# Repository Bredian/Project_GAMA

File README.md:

# Project_GAMA

We are making 8-bit game system on AVR.

Roles on this project as follows:

Gruzdev Fedor - SID chip programming (asm) and general hardware design - Attiny45

Krylov Alexander - Main Processing Unit programming (C lang (+asm maybe)) - Atmega (model unknown for now)

Savostenok Zlata - Controller interface programming (C lang) - Attiny45 + 7400 series logic

Buchnev Arseniy - Hardware maintenance and soldering

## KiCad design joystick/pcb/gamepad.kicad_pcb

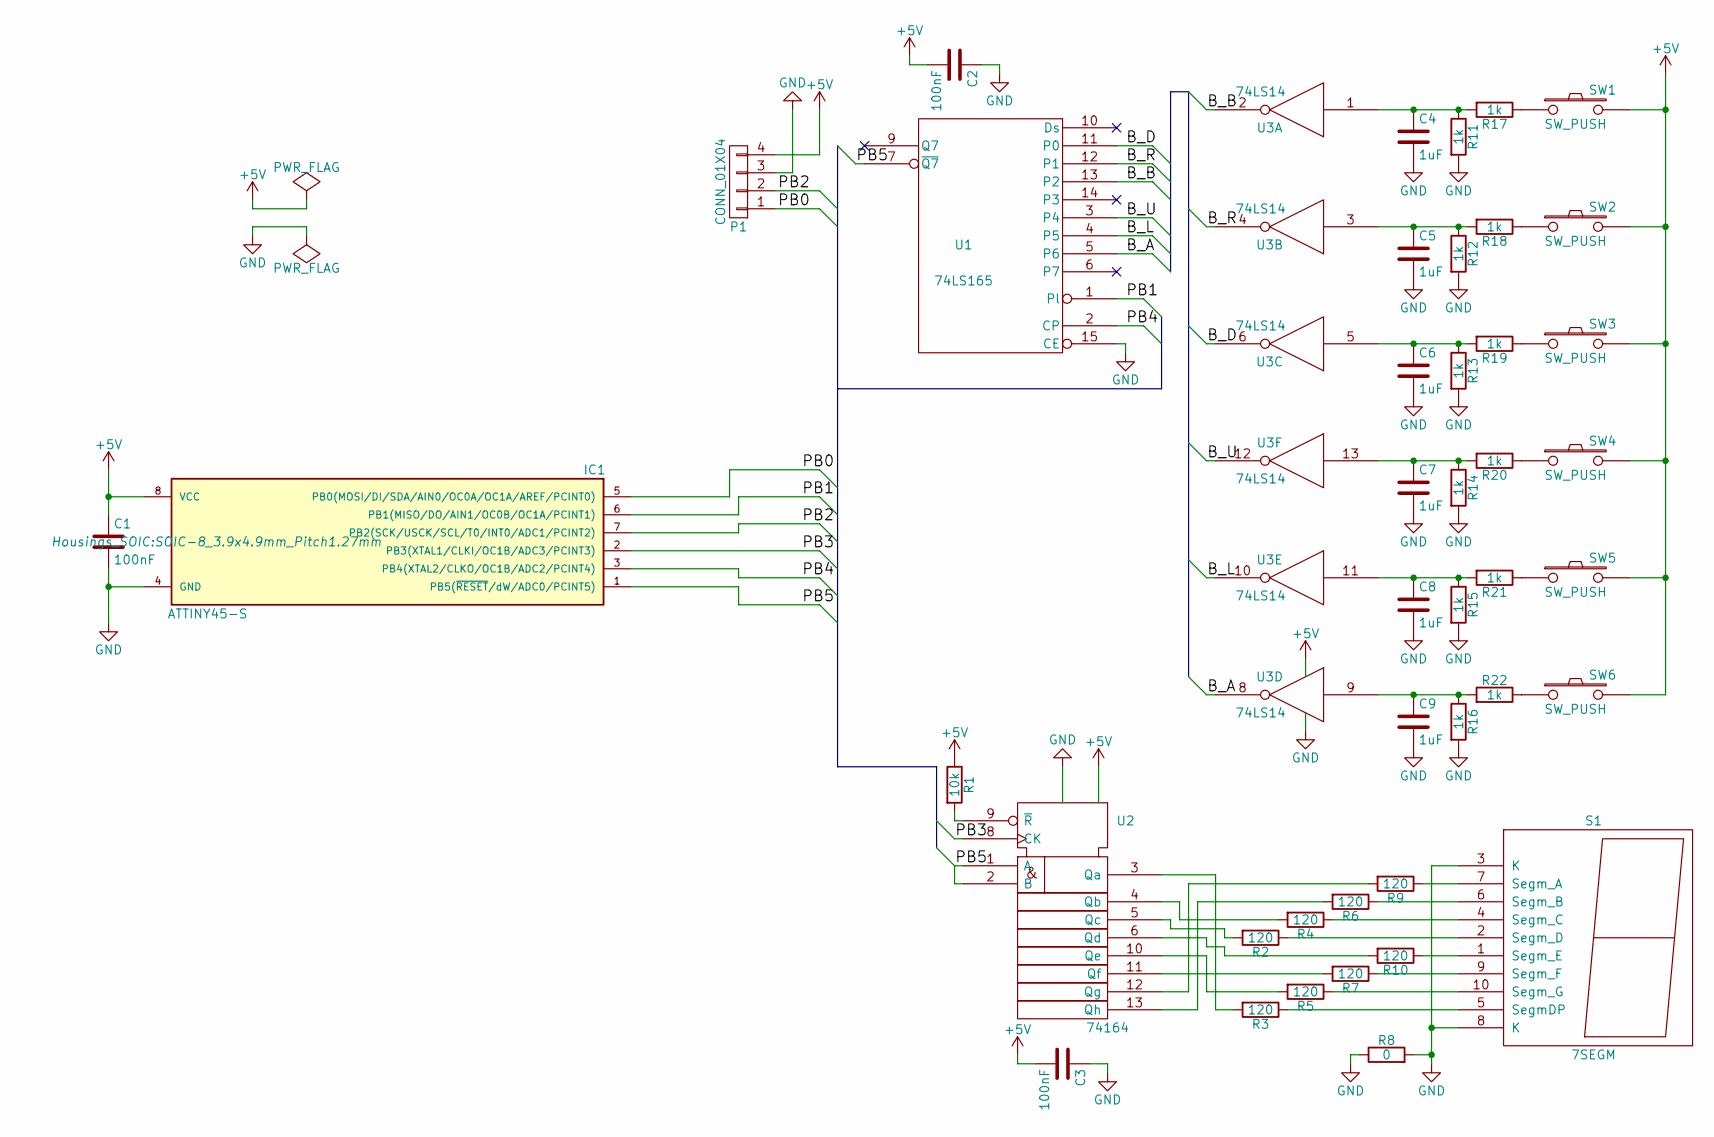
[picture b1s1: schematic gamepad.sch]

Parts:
C1, C2, C3: 100nF; C_0805_HandSoldering
C4, C5, C6, C7, C8, C9: 1uF; C_0805_HandSoldering
IC1: ATTINY45-S; SOIC-8_3.9x4.9mm_Pitch1.27mm
P1: CONN_01X04; Pin_Header_Angled_1x04
R1: 10k; R_0805_HandSoldering
R2, R3, R4, R5, R6, R7, R9, R10: 120; R_0805_HandSoldering
R8: 0; R_0805_HandSoldering
R11, R12, R13, R14, R15, R16, R17, R18, R19, R20, R21, R22: 1k; R_0805_HandSoldering
S1: 7SEGM; 7SegmentLED_LTS6760_LTS6780
SW1, SW2, SW3, SW4, SW5, SW6: SW_PUSH; SW_PUSH_SMALL
U1: 74LS165; SO-16-N
U2: 74164; SOIC-14_3.9x8.7mm_Pitch1.27mm
U3: 74LS14; SOIC-14_3.9x8.7mm_Pitch1.27mm

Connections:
+5V: C1.1, C2.2, C3.2, IC1.8 (VCC), P1.4, R1.1, SW1.2, SW2.2, SW3.2, SW4.2, SW5.2, SW6.2, U1.16 (VCC), U2.14 (Vdd), U3.14 (VCC)
/B_A: U1.5 (P6), U3.8
/B_B: U1.13 (P2), U3.2
/B_D: U1.11 (P0), U3.6
/B_L: U1.4 (P5), U3.10
/B_R: U1.12 (P1), U3.4
/B_U: U1.3 (P4), U3.12
/PB0: IC1.5 (PB0(MOSI/DI/SDA/AIN0/OC0A/OC1A/AREF/PCI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), P1.1
/PB1: IC1.6 (PB1(MISO/DO/AIN1/OC0B/OC1A/PCINT1)), U1.1 (Pl)
/PB2: IC1.7 (PB2(SCK/USCK/SCL/T0/INT0/ADC1/PCINT2)), P1.2
/PB3: IC1.2 (PB3(XTAL1/CLKI/OC1B/ADC3/PCINT3)), U2.8 (CK)
/PB4: IC1.3 (PB4(XTAL2/CLKO/OC1B/ADC2/PCINT4)), U1.2 (CP)
/PB5: IC1.1 (PB5(~RESET~/dW/ADC0/PCINT5)), U1.7 (~Q7), U2.1 (A), U2.2 (B)
GND: C1.2, C2.1, C3.1, C4.2, C5.2, C6.2, C7.2, C8.2, C9.2, IC1.4 (GND), P1.3, R8.1, R8.2, R11.2, R12.2, R13.2, R14.2, R15.2, R16.2, S1.3 (K), S1.8 (K), U1.8 (GND), U1.15 (CE), U2.7 (Vss), U3.7 (GND)
unnamed: C4.1, R11.1, R17.2, U3.1
unnamed: C5.1, R12.1, R18.2, U3.3
unnamed: C6.1, R13.1, R19.2, U3.5
unnamed: C7.1, R14.1, R20.2, U3.13
unnamed: C8.1, R15.1, R21.2, U3.11
unnamed: C9.1, R16.1, R22.2, U3.9
unnamed: R1.2, U2.9 (~R)
unnamed: R2.1, S1.2 (Segm_D)
unnamed: R2.2, U2.5 (Qc)
unnamed: R3.1, S1.5 (SegmDP)
unnamed: R3.2, U2.3 (Qa)
unnamed: R4.1, S1.4 (Segm_C)
unnamed: R4.2, U2.4 (Qb)
unnamed: R5.1, S1.10 (Segm_G)
unnamed: R5.2, U2.10 (Qe)
unnamed: R6.1, S1.6 (Segm_B)
unnamed: R6.2, U2.13 (Qh)
unnamed: R7.1, S1.9 (Segm_F)
unnamed: R7.2, U2.11 (Qf)
unnamed: R9.1, S1.7 (Segm_A)
unnamed: R9.2, U2.12 (Qg)
unnamed: R10.1, S1.1 (Segm_E)
unnamed: R10.2, U2.6 (Qd)
unnamed: R17.1, SW1.1
unnamed: R18.1, SW2.1
unnamed: R19.1, SW3.1
unnamed: R20.1, SW4.1
unnamed: R21.1, SW5.1
unnamed: R22.1, SW6.1

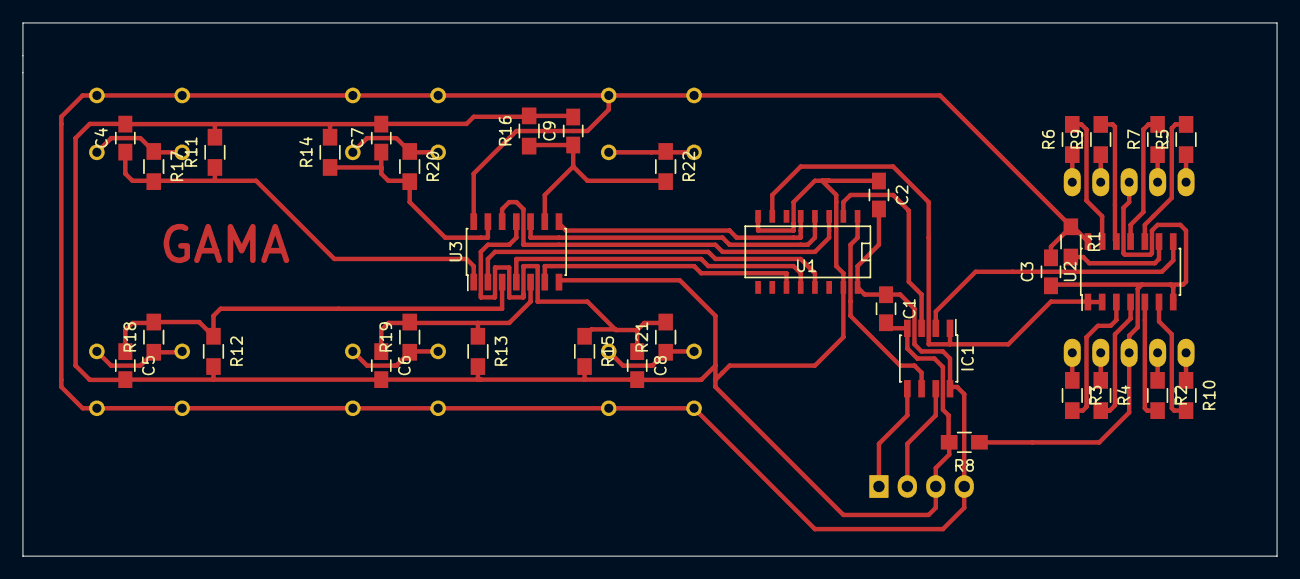
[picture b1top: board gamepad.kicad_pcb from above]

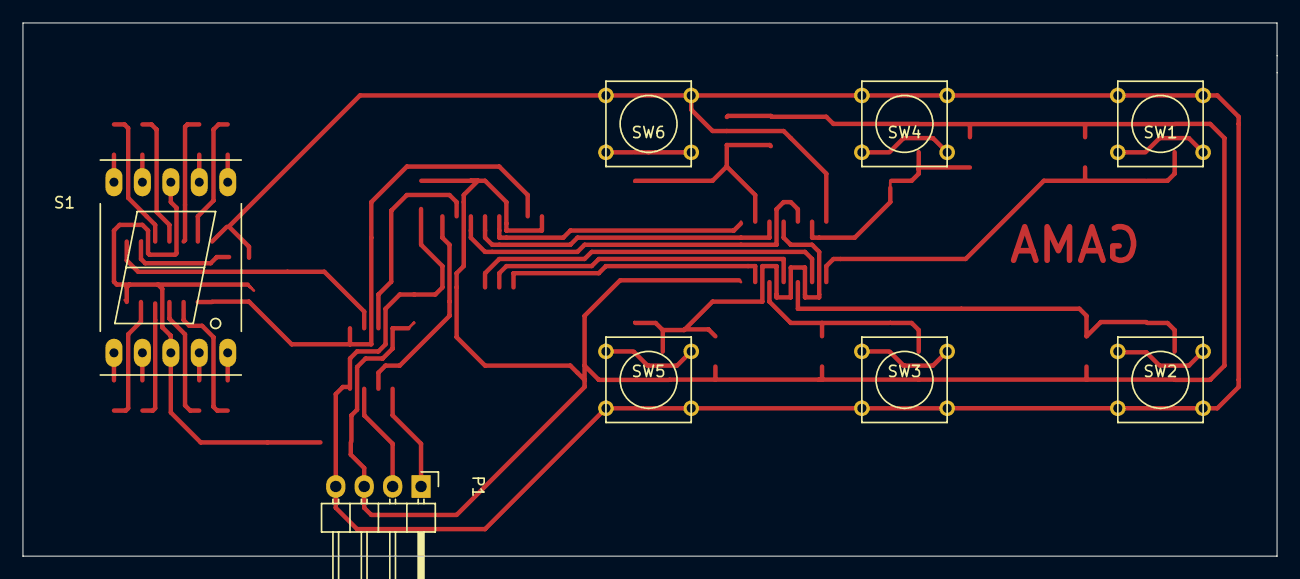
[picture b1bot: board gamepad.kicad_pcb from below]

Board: 2 copper layers, 112.0 x 47.6 mm, 43 parts (8 on the bottom side), 43 nets.

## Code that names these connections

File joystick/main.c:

#include <avr/io.h>
#include <avr/interrupt.h>
#include <avr/cpufunc.h>
#include "USI_TWI_Slave.h"

#define SLAVE_ADDR 0x02

#define SAMPLE PB1
#define CLK_7SEG PB3
#define CLK_BUT PB4
#define DATA PB5


void main(void) __attribute__((noreturn));
uint8_t read_buttons(void);
void set_7seg(uint8_t num);


void main(void) {
	
	uint8_t tmp;
	
	DDRB = (1 << SAMPLE)|(1 << CLK_7SEG)|(1 << CLK_BUT)|(0 << DATA);//port directions
	PORTB = (1 << SAMPLE)|(1 << CLK_7SEG)|(1 << CLK_BUT);			//initial port states
	
	USI_TWI_Slave_Initialise(SLAVE_ADDR);
	
	sei();
	
	while(1) {
		
		if(USI_TWI_Data_In_Receive_Buffer())
			{
				tmp = USI_TWI_Receive_Byte();
				set_7seg(tmp);
			}
		
		tmp = read_buttons();
		USI_TWI_Transmit_Byte(tmp);	//not actually transmit, but put in buffer in order to transmit
	}
	
}


uint8_t read_buttons(void) {
	uint8_t buttons = 0, tmp = 0, i;
	
	DDRB &= ~(1 << DATA);			//will receive data
	
	PORTB &= ~(1 << SAMPLE);		//sampling buttons
	_NOP();
	_NOP();
	PORTB |= (1 << SAMPLE);
	
	PORTB &= ~(1 << CLK_BUT);		//clock goes down
	
	i = 0;
	
	while(i < 8) {
		PORTB |= (1 << CLK_BUT);	//clock goes up, data are clocked out of SR
		_NOP();
		_NOP();
		PORTB &= ~(1 << CLK_BUT);	//clock goes down
		
		tmp >>= 1;
		
		if((PORTB & (1 << DATA)) == 1)//getting data
			tmp |= (1 << 7);
		else
			tmp &= ~(1 << 7);
		
		i++;
	}
									//now we have buttons' state in tmp, LSB is P7 of SR
	
										//magic numbers! actually, we shake bits to get them in right places
	buttons |= (tmp & (1 << 5)) << 5;	//up
	buttons |= (tmp & (1 << 7)) << 4;	//down
	buttons |= (tmp & (1 << 6)) << 3;	//left
	buttons |= (tmp & (1 << 3)) << 2;	//right
	buttons |= (tmp & (1 << 2)) << 1;	//A
	buttons |= (tmp & (1 << 1)) << 0;	//B
	
	return buttons; 
}


void set_7seg(uint8_t num) {
	uint8_t tmp = 0;
	uint8_t i;
	
	tmp = (num & (1 << 4)) << 3;		//magic begins; tmp's MSB is dot
										//the only thing left now is number to display
	switch(num & 0b00001111) {					//loads of magic numbers follow. don't worry, it's just numbers to display 
		case 0: tmp = tmp | 0b01110111;
			break;
		case 1: tmp = tmp | 0b01000001;
			break;
		case 2: tmp = tmp | 0b00111011;
			break;
		case 3: tmp = tmp | 0b01101011;
			break;
		case 4: tmp = tmp | 0b01001101;
			break;
		case 5: tmp = tmp | 0b01101110;
			break;
		case 6: tmp = tmp | 0b01111110;
			break;
		case 7: tmp = tmp | 0b01000011;
			break;
		case 8: tmp = tmp | 0b01111111;
			break;
		case 9: tmp = tmp | 0b01101111;
			break;
		case 0x0a: tmp = tmp | 0b01011111;
			break;
		case 0x0b: tmp = tmp | 0b01111100;
			break;
		case 0x0c: tmp = tmp | 0b00110110;
			break;
		case 0x0d: tmp = tmp | 0b01111001;
			break;
		case 0x0e: tmp = tmp | 0b00111110;
			break;
		case 0x0f: tmp = tmp | 0b00011110;
			break;
	}
	
	DDRB |= (1 << DATA);			//now we send data
	for(i = 0; i < 8; i++) {		//shifting data out. LSB goes first
		PORTB &= ~(1 << CLK_7SEG);	//clock goes down
		if ((tmp & 1) == 1) PORTB |= (1 << DATA);
			else PORTB &= ~(1 << DATA);	//putting data bit on DATA
		_NOP();
		_NOP();
		PORTB |= (1 << CLK_7SEG);	//clock goes up, shifting our data bit out
	}
	
	return;
}

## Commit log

2017-02-19 Create Prototype
2017-03-07 INIT
    Added dirs for every part and current results.
2017-03-07 Added specs for SID and joystick
2017-03-13 Updated joystick's circuit
2017-04-03 Fixed hardware bug (74LS14 inputs were left floating) Changed schematics accordingly
2017-04-10 wrote part of TWI logic buffer operations and main interrupt are left also decided on slave address (0x03)
2017-04-12 wrote all TWI (I2C) parts mapped memory
2017-04-17 little optimization for TWI as we only send 1 byte, receiving part can be shortened a bit
2017-04-21 Modified TWI handler Wrote main program sceleton
2017-05-03 Started writing firmware. TWI communication - done (code from Atmel AVR312 Application Note). 7 segment - done. buttons - TODO. Makefile - TODO.
2017-05-04 finished firmware small fix in pcb to get buttons in right order TODO: Makefile
2017-05-16 everything is done awaiting flashing and debugging
2017-05-23 checked all files wrote makefile partially compiles
2017-05-23 tried to fix joystick's firmware
2017-05-23 Update Makefile
2017-05-23 tried to fix core's firmware
2017-05-23 getting ready to merge with joystick
2017-10-21 looked at Piano.ino
2017-10-21 splitted notes[][] array
2017-10-21 fixed piano_play
